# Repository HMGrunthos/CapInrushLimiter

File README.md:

# CapInrushLimiter
Inspiration:
* [This answer](https://electronics.stackexchange.com/questions/80365/capacitor-inrush-current/80428#80428)
* [And this question](https://electronics.stackexchange.com/questions/163939/inrush-current-limiter-design-questions-review)

Schematics:
* [Model schematic](ModelSchematic.pdf)
* [PCB schematic](CapInrushLimBB/CapInrushLimiter.pdf)

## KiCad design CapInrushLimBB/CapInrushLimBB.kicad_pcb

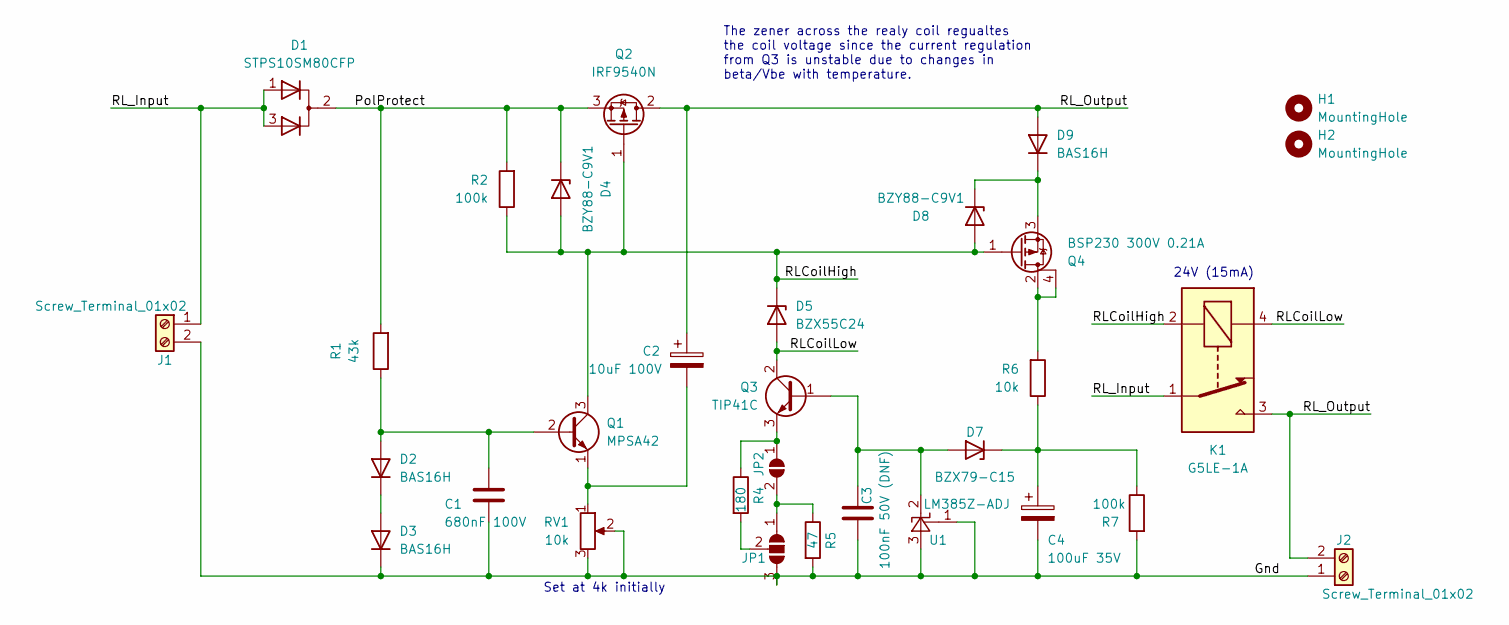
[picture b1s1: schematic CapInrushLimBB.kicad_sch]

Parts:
C1: 680nF 100V; C_Disc_D5.1mm_W3.2mm_P5.00mm
C2: 10uF 100V; CP_Radial_D6.3mm_P2.50mm
C3: 100nF 50V (DNF); C_Disc_D5.1mm_W3.2mm_P5.00mm
C4: 100uF 35V; CP_Radial_D6.3mm_P2.50mm
D1: STPS10SM80CFP; TO-220F-3_Vertical
D2, D3, D9: BAS16H; D_SOD-323_HandSoldering
D4: BZY88-C9V1; D_DO-35_SOD27_P3.81mm_Vertical_AnodeUp
D5: BZX55C24; D_DO-35_SOD27_P2.54mm_Vertical_KathodeUp
D7: BZX79-C15; D_DO-35_SOD27_P3.81mm_Vertical_AnodeUp
D8: BZY88-C9V1; D_DO-35_SOD27_P2.54mm_Vertical_AnodeUp
H1, H2: MountingHole; MountingHole_3.2mm_M3
J1, J2: Screw_Terminal_01x02; TerminalBlock_Altech_AK300-2_P5.00mm
JP1: SolderJumper_3_Open; SolderJumper-3_P1.3mm_Open_RoundedPad1.0x1.5mm
JP2: SolderJumper_2_Open; SolderJumper-2_P1.3mm_Open_RoundedPad1.0x1.5mm
K1: G5LE-1A; Relay_SPST-NO_Omron-G5LE-1A
Q1: MPSA42; TO-92_Inline
Q2: IRF9540N; TO-220-3_Vertical
Q3: TIP41C; TO-220-3_Vertical
Q4: BSP230 300V 0.21A; SOT-223
R1: 43k; R_Axial_DIN0207_L6.3mm_D2.5mm_P2.54mm_Vertical
R2, R7: 100k; R_Axial_DIN0207_L6.3mm_D2.5mm_P2.54mm_Vertical
R4: 180; R_Axial_DIN0207_L6.3mm_D2.5mm_P2.54mm_Vertical
R5: 47; R_Axial_DIN0207_L6.3mm_D2.5mm_P2.54mm_Vertical
R6: 10k; R_Axial_DIN0207_L6.3mm_D2.5mm_P2.54mm_Vertical
RV1: 10k; Potentiometer_Bourns_3296W_Vertical
U1: LM385Z-ADJ; TO-92_Inline

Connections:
/Gnd: C1.2, C3.1, C4.2, D3.1 (K), J1.2, J2.1, JP1.3 (B), R5.2, R7.2, RV1.2, RV1.3, U1.1 (FB), U1.3 (A)
/PolProtect: D1.2 (A), D4.1 (K), Q2.3 (S), R1.2, R2.2
/RLCoilHigh: D4.2 (A), D5.1 (K), D8.2 (A), K1.2, Q1.3 (C), Q2.1 (G), Q4.1 (G), R2.1
/RLCoilLow: D5.2 (A), K1.4, Q3.2 (C)
/RL_Input: D1.1 (K), D1.3 (K), J1.1, K1.1
/RL_Output: C2.1, D9.2 (A), J2.2, K1.3, Q2.2 (D)
unnamed: C1.1, D2.2 (A), Q1.2 (B), R1.1
unnamed: C2.2, Q1.1 (E), RV1.1
unnamed: C3.2, D7.2 (A), Q3.1 (B), U1.2 (K)
unnamed: C4.1, D7.1 (K), R6.1, R7.1
unnamed: D2.1 (K), D3.2 (A)
unnamed: D8.1 (K), D9.1 (K), Q4.3 (S)
unnamed: JP1.1 (A), JP2.2 (B), R5.1
unnamed: JP1.2 (C), R4.2
unnamed: JP2.1 (A), Q3.3 (E), R4.1
unnamed: Q4.2 (D), Q4.4 (D), R6.2

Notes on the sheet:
The zener across the realy coil regualtes the coil voltage since the current regulation from Q3 is unstable due to changes in beta/Vbe with temperature.
24V (15mA)
Set at 4k initially

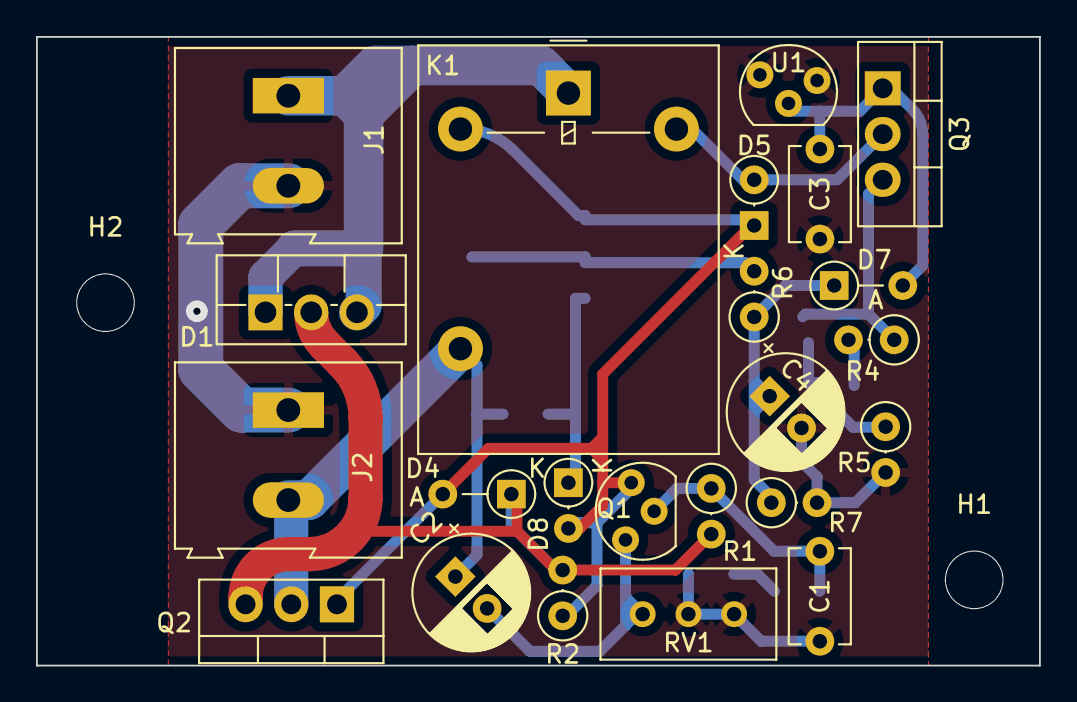
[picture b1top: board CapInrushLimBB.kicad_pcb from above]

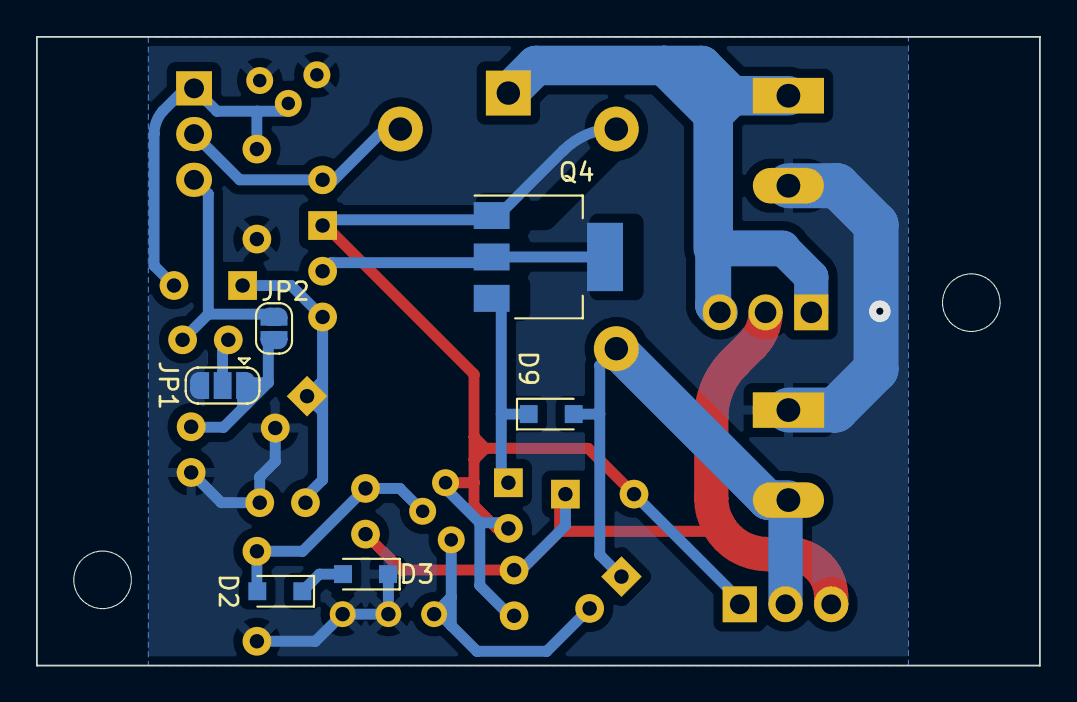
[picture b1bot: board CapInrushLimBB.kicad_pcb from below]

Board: 2 copper layers, 55.7 x 34.9 mm, 31 parts (6 on the bottom side), 16 nets.

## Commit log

2022-08-29 Included the right files
2022-08-29 Added reverse polarity MOSFET
2022-08-29 Working soft starter
2022-08-29 Added relay latching and changed diode.
2022-08-30 Fixed gate protection on relay driver MOSFET
2022-08-30 Fixed gate protection on relay driver
2022-08-30 Renamed first model and tried a different topology.
2022-08-31 Tweaks to the new design.
2022-09-01 Updated seconds version with relay driver.
2022-09-03 Simplifications.
2022-09-03 Final updates before timer version
2022-09-05 Added relay delay circuit.
2022-09-05 Tidied up schematic.
2022-09-05 Added extra diode on the main FET drive and changed the relay driver transistor.
2022-09-07 Added initial version of schematic
2022-09-07 Connected up schematic prior to finalising component choice.
2022-09-08 Updated component values/types (no footprints yet)
2022-09-08 Tweaked layout in schematic.
2022-09-09 Started footprint assignment.
2022-09-09 Finished initial footprint assignment.
2022-09-09 Tweaked component values (names) and checked footprints.
2022-09-09 Started layout.
2022-09-11 Simplified and labelled schematic and performed work on layout.
2022-09-13 Layout changes.
2022-09-14 Removed unused models.
2022-09-16 Added new current limiting relay timer.
2022-09-17 Fixed latest design - current limiting relay driver.
2022-09-18 Changed voltge limiting element to an LED.
2022-09-19 Relayed out spice model.
2022-09-19 Updated model and schematic values.
2022-09-22 Updated values and footprints.
2022-09-23 First layout complete
2022-09-23 Tweaked board outline.
2022-09-24 Fixed zener model.
2022-09-24 Added via linking top pour to Gnd.
2022-09-24 Tweaked some component orientations to give space for through board connections.
2022-09-25 Updated relay footprint and tweaked track layout so it rounds nicley.
2022-09-25 Adding library tables for symbols and footprints
2022-09-25 Updated silkscreen and design rules.
2022-09-25 Tweaked tracks for a slightly better layout.
2022-09-25 Fixed a slight clearance issue once rounded.
2022-09-25 Added bottom ground pour and tweaked a track position to lie within it.
2022-09-25 Track position
2022-09-26 Added mounting holes and adjusted board margin.
2022-09-26 Added script to copy tracks (with arcs) to the solder mask stop layer.
2022-09-26 Tweaked track widths around high current tracks.
2022-09-27 Added rounded tracks version of PCB
2022-09-27 Tweaked track position to equalise track clearance.
2022-09-27 Added first version of artwork
2022-09-27 Improved track rounding
2022-09-28 Added artwork and tweaked Gnd track in unrounded PCB
2022-09-28 Tweaked BJT footprint (custom) to increase clearance and tweaked track positions accordingly.
2022-09-28 Updated rounded tracks PCB and uploading modified TO-92 footprint (to increase clearance.)
2022-09-29 Adding updated artwork.
2022-09-29 Adding high current tracks to back mask.
2022-10-02 Updated component value.
2022-10-03 Slight track tweak following assembly.
2022-10-03 New model revision to cover lower voltage use.
2022-10-03 Updated to remove LED reference (use two diodes) and relayed out following update.
2022-10-03 Increased pad sizes on the TO92 footprint and tidied up the layout a tad.
2022-10-03 Layout tweaks.
2022-10-10 Updated rounded tracks version of updates for low voltage use.
2022-10-11 Added solder mask region.
2022-10-13 Modified schematic to support low voltage operation with 24V relay and updated board layout.
2022-10-13 Updated PCB layout of lower voltage capable inrush limiter.
2022-10-13 Added lower voltage tollerant model and started tweaking PCB layout to move pass element somewhere where it can be heat sunk.
2022-10-13 Updated footprints in schematic and layed out tracks to make pass element accessable from the side of the board.
2022-10-13 Updated layout and rounded tracks version.
2022-10-15 Removed LED and added voltage reference to better regulate the relay coil current.
2022-10-15 Changed the reference type, changed current set resistor strategy and updated PCB.
2022-10-16 Relayed out relay timer/regulator section to reduce track lengths.
2022-10-17 Tweaked track placement.
2022-10-17 Updated models for lower voltage operation.
2022-10-17 Added missing model components.
2022-10-17 Added comment text on default setting for timer pot.
2022-10-17 Updated rounded tracks version.
2022-10-17 Updated artwork.
2022-10-17 Updated to match rounded version.
2022-10-17 Added production files.
2022-10-26 Tweaked model layout.
2022-10-30 Adding test traces for rev one (with a dual diode instead of a resistive divider.)
2022-11-10 Updated values of relay current limiter resistors.
2022-11-11 Updated model, schematic and PCB to switch to use a TLV431 as a current regulator.
2022-11-11 Removed bypass cap on TLV431 as it pushes it too close to instability.
2022-11-11 Updated schematic, layout and values to better regulate the relay current.
2022-11-12 Adding TLV431 device to symbol library.
2022-11-16 Updated schematic and PCB with fixed TLV431 symbol.
2022-11-16 Updating model, schematic and PCB to remote cap. on the relay timer ref. and to fit a zener across the relay coil.
2022-11-17 Updating model, schematic and PCB to remove cap. on the relay timer ref. and to fit a zener across the relay coil.
2022-11-18 Added comments on setting timing pot and why I'm using a zener across the relay coil.
2022-11-19 Switched to lower rated 24V zener and tidied up dependent models (already on a separate branch.)
2022-11-19 Updated current limit components.
2022-11-19 Updated model values.
2022-11-21 Updated layout on original and rounded designs.
2022-11-21 Added schematic PDF and fixed typos in schematic sheet.
2022-11-24 Added model schematic PDF.
